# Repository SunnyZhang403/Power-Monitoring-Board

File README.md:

# Power-Monitoring-Board

For Arduino board files: https://github.com/Alarm-Siren/arduino-kicad-library

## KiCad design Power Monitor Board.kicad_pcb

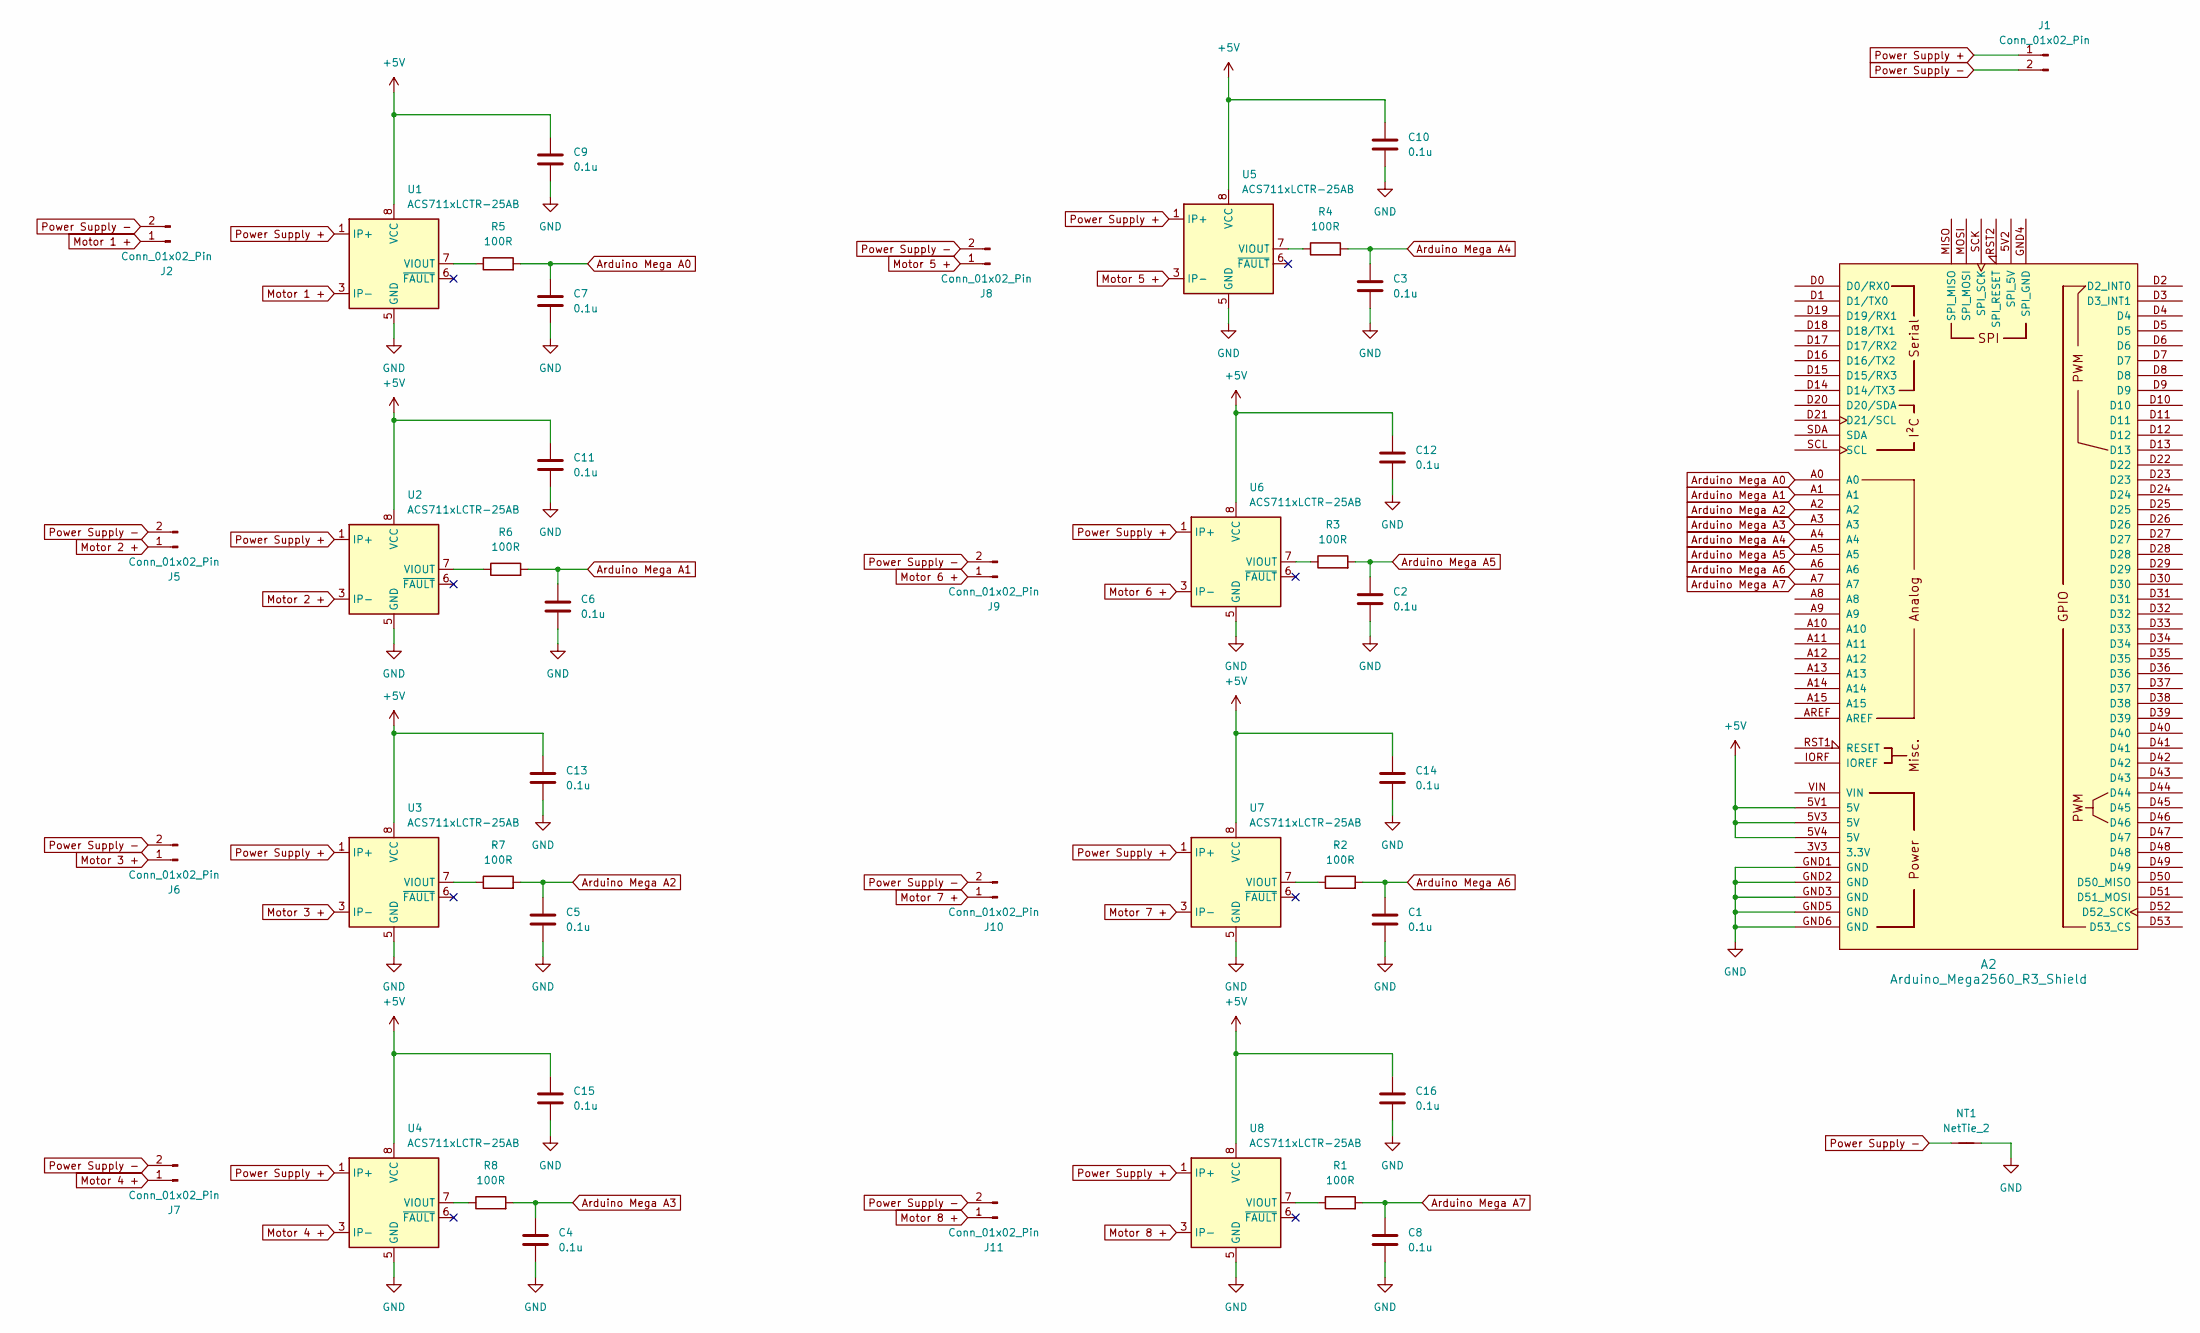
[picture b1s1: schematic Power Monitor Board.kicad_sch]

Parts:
A2: Arduino_Mega2560_R3_Shield
C1, C2, C3, C4, C5, C6, C7, C8, C9, C10, C11, C12, C13, C14, C15, C16: 0.1u; C_0603_1608Metric
J1, J2, J5, J6, J7, J8, J9, J10, J11: Conn_01x02_Pin; AMASS_XT60-M_1x02_P7.20mm_Vertical
NT1: NetTie_2; NetTie-2_SMD_Pad0.5mm
R1, R2, R3, R4, R5, R6, R7, R8: 100R; R_0603_1608Metric
U1, U2, U3, U4, U5, U6, U7, U8: ACS711xLCTR-25AB; SOIC-8_3.9x4.9mm_P1.27mm

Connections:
+5V: A2.5V1 (5V), A2.5V3 (5V), A2.5V4 (5V), C9.1, C10.1, C11.1, C12.1, C13.1, C14.1, C15.1, C16.1, U1.8 (VCC), U2.8 (VCC), U3.8 (VCC), U4.8 (VCC), U5.8 (VCC), U6.8 (VCC), U7.8 (VCC), U8.8 (VCC)
Arduino Mega A0: A2.A0, C7.1, R5.2
Arduino Mega A1: A2.A1, C6.1, R6.2
Arduino Mega A2: A2.A2, C5.1, R7.2
Arduino Mega A3: A2.A3, C4.1, R8.2
Arduino Mega A4: A2.A4, C3.1, R4.2
Arduino Mega A5: A2.A5, C2.1, R3.2
Arduino Mega A6: A2.A6, C1.1, R2.2
Arduino Mega A7: A2.A7, C8.1, R1.2
Arduino Mega A8: A2.A8; also elsewhere on the board
GND: A2.GND1 (GND), A2.GND2 (GND), A2.GND3 (GND), A2.GND5 (GND), A2.GND6 (GND), C1.2, C2.2, C3.2, C4.2, C5.2, C6.2, C7.2, C8.2, C9.2, C10.2, C11.2, C12.2, C13.2, C14.2, C15.2, C16.2, NT1.2, U1.5 (GND), U2.5 (GND), U3.5 (GND), U4.5 (GND), U5.5 (GND), U6.5 (GND), U7.5 (GND), U8.5 (GND); also elsewhere on the board
Motor 1 +: J2.1, U1.3 (IP-), U1.4 (IP-)
Motor 2 +: J5.1, U2.3 (IP-), U2.4 (IP-)
Motor 3 +: J6.1, U3.3 (IP-), U3.4 (IP-)
Motor 4 +: J7.1, U4.3 (IP-), U4.4 (IP-)
Motor 5 +: J8.1, U5.3 (IP-), U5.4 (IP-)
Motor 6 +: J9.1, U6.3 (IP-), U6.4 (IP-)
Motor 7 +: J10.1, U7.3 (IP-), U7.4 (IP-)
Motor 8 +: J11.1, U8.3 (IP-), U8.4 (IP-)
unnamed: R5.1, U1.7 (VIOUT)
unnamed: R6.1, U2.7 (VIOUT)
unnamed: R7.1, U3.7 (VIOUT)
unnamed: R8.1, U4.7 (VIOUT)
unnamed: R4.1, U5.7 (VIOUT)
unnamed: R3.1, U6.7 (VIOUT)
unnamed: R2.1, U7.7 (VIOUT)
unnamed: R1.1, U8.7 (VIOUT)
Power Supply +: J1.1, U1.1 (IP+), U1.2 (IP+), U2.1 (IP+), U2.2 (IP+), U3.1 (IP+), U3.2 (IP+), U4.1 (IP+), U4.2 (IP+), U5.1 (IP+), U5.2 (IP+), U6.1 (IP+), U6.2 (IP+), U7.1 (IP+), U7.2 (IP+), U8.1 (IP+), U8.2 (IP+); also elsewhere on the board
Power Supply -: J1.2, J2.2, J5.2, J6.2, J7.2, J8.2, J9.2, J10.2, J11.2, NT1.1

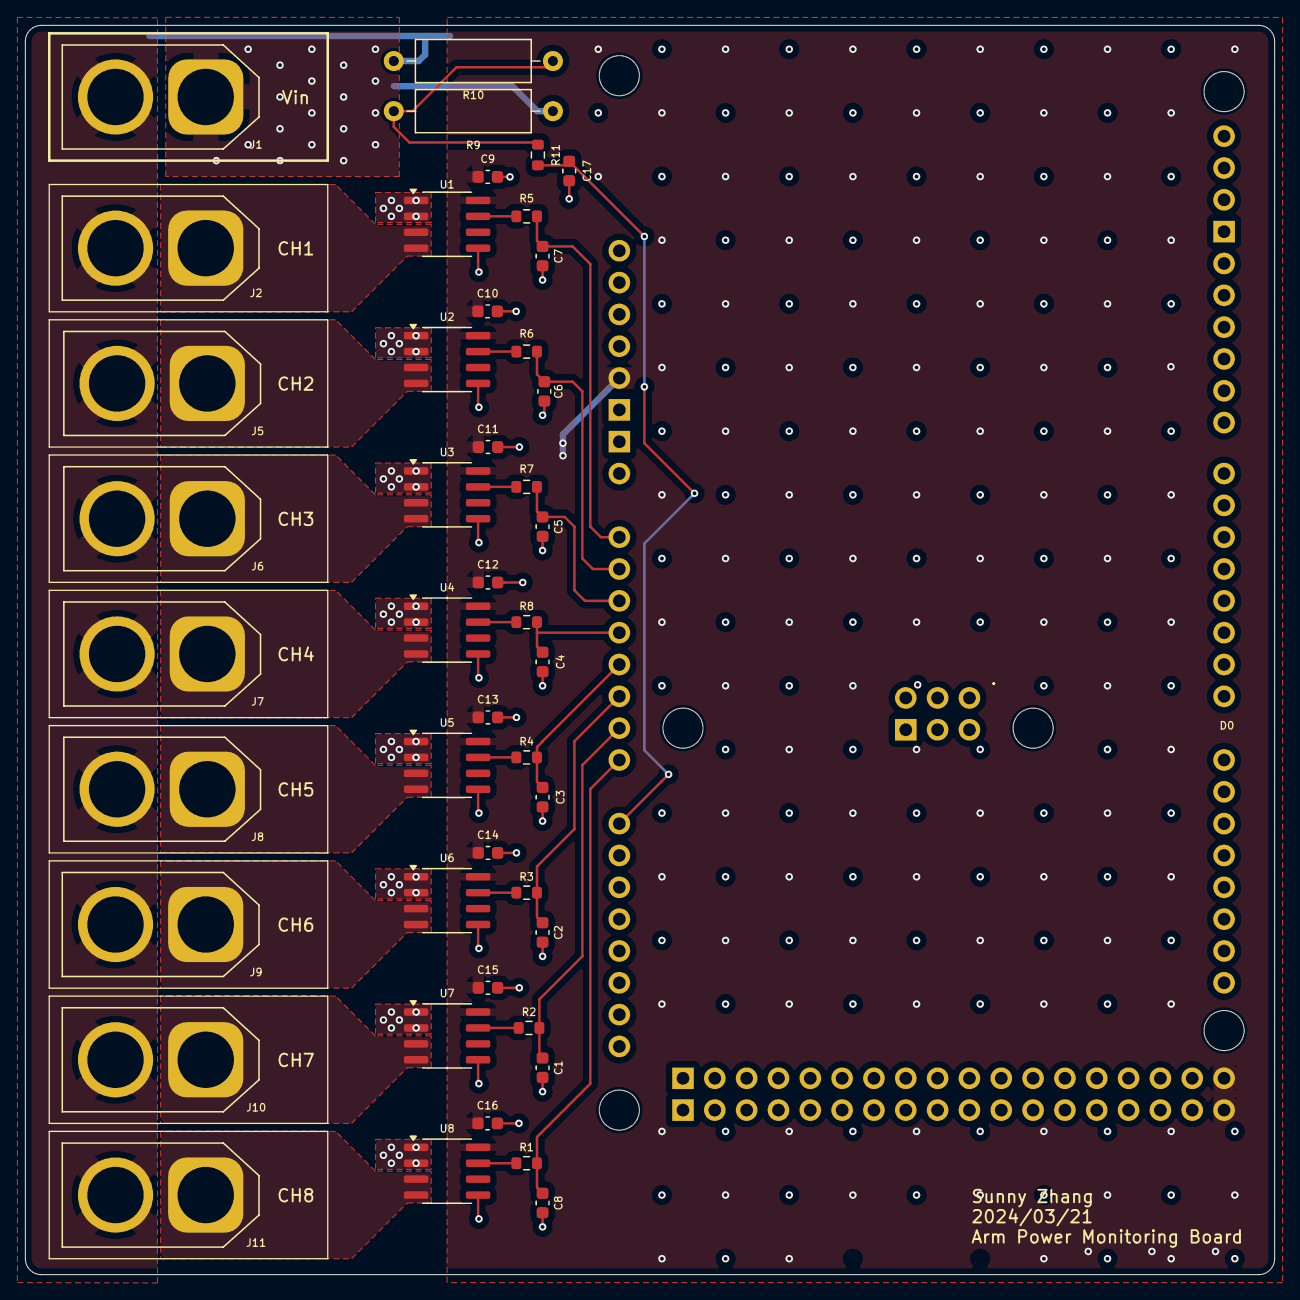
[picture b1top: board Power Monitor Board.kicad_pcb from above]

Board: 2 copper layers, 99.7 x 99.7 mm, 47 parts (1 on the bottom side), 30 nets.

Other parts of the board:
C17: 0.1u; C_0603_1608Metric
R9, R10: R; R_Axial_DIN0309_L9.0mm_D3.2mm_P12.70mm_Horizontal
R11: 100R; R_0603_1608Metric

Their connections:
Arduino Mega A8: C17.1, R11.2; also elsewhere on the board
GND: C17.2, R10.2; also elsewhere on the board
unnamed: R9.2, R10.1, R11.1
Power Supply +: R9.1; also elsewhere on the board

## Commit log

2024-03-21 Cleaned up schematic and started layout
